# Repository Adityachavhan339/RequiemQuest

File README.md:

# RequiemQuest
RequiemQuest is custom portable handheld video game console

## Core Features
*   **The Brain:** Powered by a **Raspberry Pi Pico H**.
*   **Vibrant Display:** Features a **1.8-inch SPI TFT Color Screen (ST7735 Driver, 128x160 resolution)** operating over high-speed hardware SPI.
*   **Integrated LiPo Power Management:** Upgraded from a standard tethered USB device to a truly portable console utilizing an onboard **TP4056 lithium battery charging IC**. The system automatically powers the device and safely charges an attached 3.7V LiPo cell when micro-USB is plugged in.
*   **Ergonomic Layout & Control:** Built on a classic D-Pad layout (Up, Down, Left, Right) alongside an Action button.
*   **Chiptune Audio Synthesizer:** Includes a passive piezo buzzer driven by hardware PWM frequencies to parse and play polyphonic 8-bit theme music and in-game collision sound effects.

##BOM Table
| Part Description | Qty | Unit Price | Total Price | Vendor | Purpose / Function |
| :--- | :---: | :---: | :---: | :--- | :--- |
| **Raspberry Pi Pico (RP2040 Pre-soldered Headers)** | 1 | \$4.80 | \$4.80 | Sharvi Electronics | The Brain / Main Microcontroller |
| **1.8 Inch SPI 128x160 TFT LCD Display Module** | 1 | \$3.78 | \$3.78 | Robu | Primary Game Display |
| **Tactile Push Button Switch 6x6x5 (Pack of 10)** | 1 | \$0.20 | \$0.20 | Robu | Gamepad Input Array |
| **PCB Mounted Passive Buzzer Module** | 1 | \$0.31 | \$0.31 | Robu | Chiptune Sound Effects |
| **TP4056 Adjustable 1A Li-ion Charging Module** | 1 | \$0.20 | \$0.20 | Robu | Power Management & Battery Charger |
| **WLY501014 3.7V 50mAh 1S LiPo Battery** | 1 | \$1.73 | \$1.73 | Robu | Portable Power Source |
| **Slide Switch SS-12D00 1P2T** | 6 | \$0.02 | \$0.12 | Robu | Main Console Power Switch |
| **2.54mm 2x40 Pin Male Straight Header Strip** | 1 | \$0.13 | \$0.13 | Robu | Interconnect & Expansion Pins |
| **1N5819 Schottky Diode (DO-41)** | 1 | \$0.12 | \$0.12 | Robu | Reverse Polarity & Power Selection Diode |
| **2kΩ Resistor Network Array (0603x4)** | 1 | \$0.01 | \$0.01 | Robu | Circuit Resistor Tuning |
| **TDK 10uF 100V X7R Ceramic Capacitors (1210 SMD)** | 2 | \$0.30 | \$0.60 | Robu | Power Smoothing & Circuit Protection |
| **Custom Fabricated 2-Layer PCB** | 1 | \$9.95 | \$9.95 | Zbotic | Main System Interconnect Board |
| **💰 TOTAL** | | | **\$21.95**

##Few Images
Schematic:

PCB:

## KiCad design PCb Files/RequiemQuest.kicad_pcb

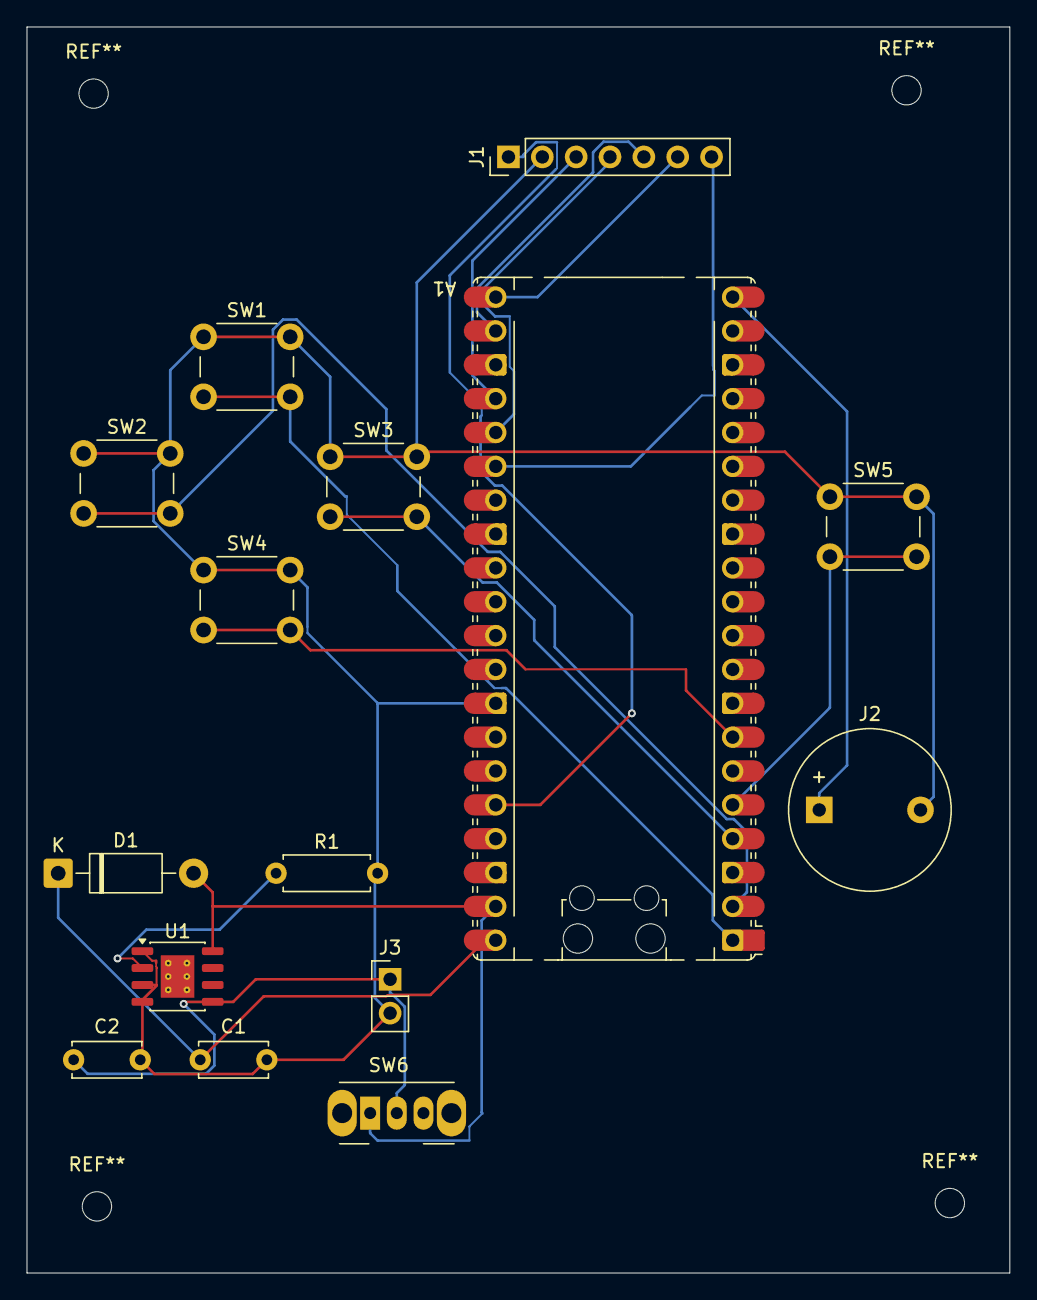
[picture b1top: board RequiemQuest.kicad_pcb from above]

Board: 2 copper layers, 73.8 x 93.5 mm, 15 parts (0 on the bottom side), 17 nets.

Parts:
A1: RaspberryPi_Pico; RaspberryPi_Pico_Common_Unspecified
C1: FC1; C_Disc_D5.0mm_W2.5mm_P5.00mm
C2: FC2; C_Disc_D5.0mm_W2.5mm_P5.00mm
D1: Power Selector Diode; D_DO-41_SOD81_P10.16mm_Horizontal
J1: TFT_DISPLAY; PinHeader_1x07_P2.54mm_Vertical
J2: BUZZER; Buzzer_12x9.5RM7.6
J3: Battery Connector; PinHeader_1x02_P2.54mm_Vertical
R1: Charge Current Resistor; R_Axial_DIN0207_L6.3mm_D2.5mm_P7.62mm_Horizontal
SW1: UP; SW_PUSH_6mm
SW2: Left; SW_PUSH_6mm
SW3: Right; SW_PUSH_6mm
SW4: DOWN; SW_PUSH_6mm
SW5: ACTION; SW_PUSH_6mm
SW6: Power Switch; SW_Slide_SPDT_Angled_CK_OS102011MA1Q
U1: TP4056-42-ESOP8 The Charger Chip; SOIC-8-1EP_3.9x4.9mm_P1.27mm_EP2.514x3.2mm_ThermalVias

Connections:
+3V3: A1.36 (3V3), J1.1
GND: A1.33 (AGND), C1.2, C2.2, J1.2, J2.2, J3.2, R1.2, SW1.1, SW2.1, SW3.1, SW4.1, SW5.1, U1.1 (TEMP), U1.3 (GND), U1.4 (V_{CC})
unnamed: A1.1 (GPIO0), SW1.2
unnamed: A1.2 (GPIO1), SW2.2
unnamed: A1.4 (GPIO2), SW3.2
unnamed: A1.5 (GPIO3), SW5.2
unnamed: A1.7 (GPIO5), SW4.2
unnamed: A1.20 (GPIO15), J2.1
unnamed: A1.21 (GPIO16), J1.6
unnamed: A1.22 (GPIO17), J1.5
unnamed: A1.24 (GPIO18), J1.3
unnamed: A1.25 (GPIO19), J1.4
unnamed: A1.26 (GPIO20), J1.7
unnamed: A1.40 (VBUS), C1.1, D1.1 (K)
unnamed: A1.39 (VSYS), D1.2 (A), SW6.1 (A), U1.8 (CE)
unnamed: C2.1, J3.1, SW6.2 (B), U1.5 (BAT)
unnamed: R1.1, U1.2 (PROG)
